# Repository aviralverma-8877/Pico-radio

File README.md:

# Raspberry Pi Pico Radio built on top of RDA5807

This project uses code from https://github.com/vmilea/pico_rda5807
Additionally it provide support for OLED display and handle GPIO input and output
for controlling an on board LED and Tact Switch.

For OLED display, This project uses pi_pico_ss_oled library from https://github.com/martinkooij/pi-pico-ss-oled

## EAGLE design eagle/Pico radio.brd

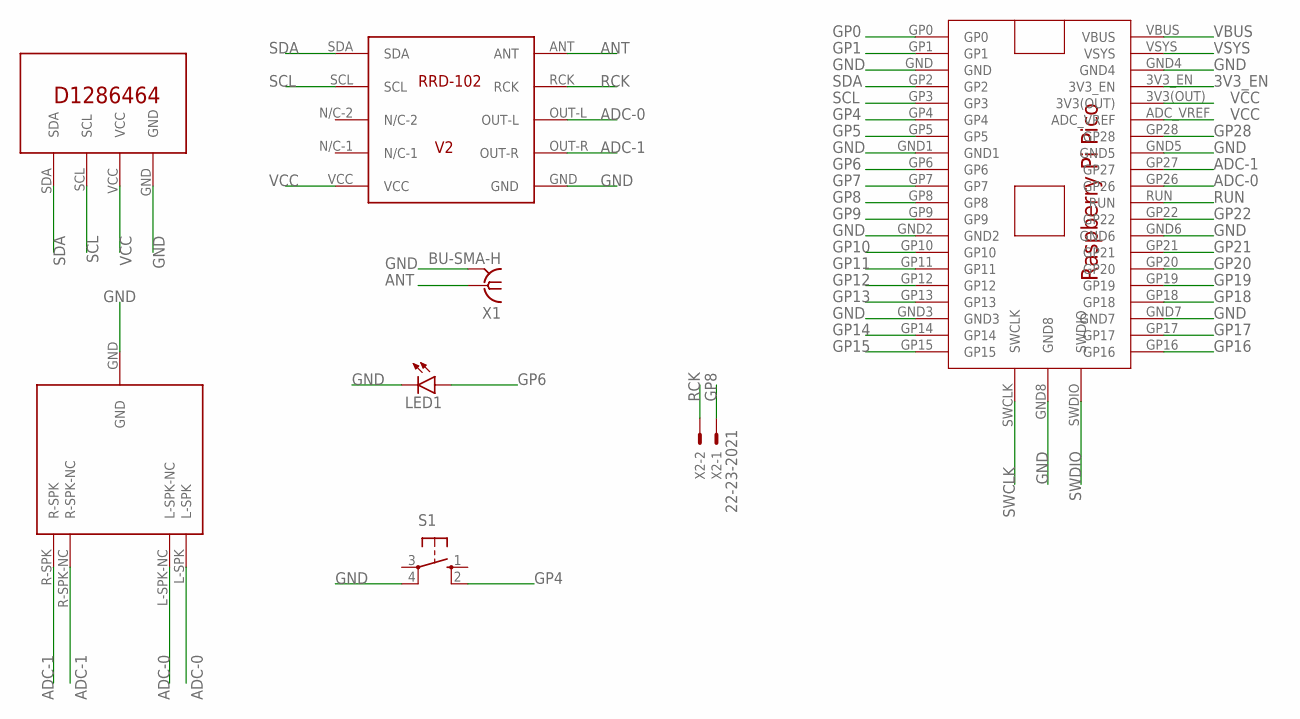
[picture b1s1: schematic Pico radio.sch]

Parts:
LED1: LED3MM
S1: 10-XX; B3F-10XX
U$1: OLED_DISPLAY
U$2: RASPBERRYPIPICO
U$3: RDD-V2
U$4: AUDIO_JACK
X1: BU-SMA-H
X2: 22-23-2021

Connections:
3V3_EN: U$2.3V3_EN
ADC-0: U$2.GP26, U$3.OUT-L, U$4.L-SPK, U$4.L-SPK-NC
ADC-1: U$2.GP27, U$3.OUT-R, U$4.R-SPK, U$4.R-SPK-NC
ANT: U$3.ANT, X1.1
GND: LED1.K (C), S1.4 (P1), U$1.GND, U$2.GND, U$2.GND1, U$2.GND2, U$2.GND3, U$2.GND4, U$2.GND5, U$2.GND6, U$2.GND7, U$2.GND8, U$3.GND, U$4.GND, X1.2, X1.3 (2), X1.4 (2), X1.5 (2)
GP0: U$2.GP0
GP1: U$2.GP1
GP4: S1.2 (S1), U$2.GP4
GP5: U$2.GP5
GP6: LED1.A, U$2.GP6
GP7: U$2.GP7
GP8: U$2.GP8, X2.1
GP9: U$2.GP9
GP10: U$2.GP10
GP11: U$2.GP11
GP12: U$2.GP12
GP13: U$2.GP13
GP14: U$2.GP14
GP15: U$2.GP15
GP16: U$2.GP16
GP17: U$2.GP17
GP18: U$2.GP18
GP19: U$2.GP19
GP20: U$2.GP20
GP21: U$2.GP21
GP22: U$2.GP22
GP28: U$2.GP28
RCK: U$3.RCK, X2.2
RUN: U$2.RUN
SCL: U$1.SCL, U$2.GP3, U$3.SCL
SDA: U$1.SDA, U$2.GP2, U$3.SDA
SWCLK: U$2.SWCLK
SWDIO: U$2.SWDIO
VBUS: U$2.VBUS
VCC: U$1.VCC, U$2.3V3(OUT), U$2.ADC_VREF, U$3.VCC
VSYS: U$2.VSYS

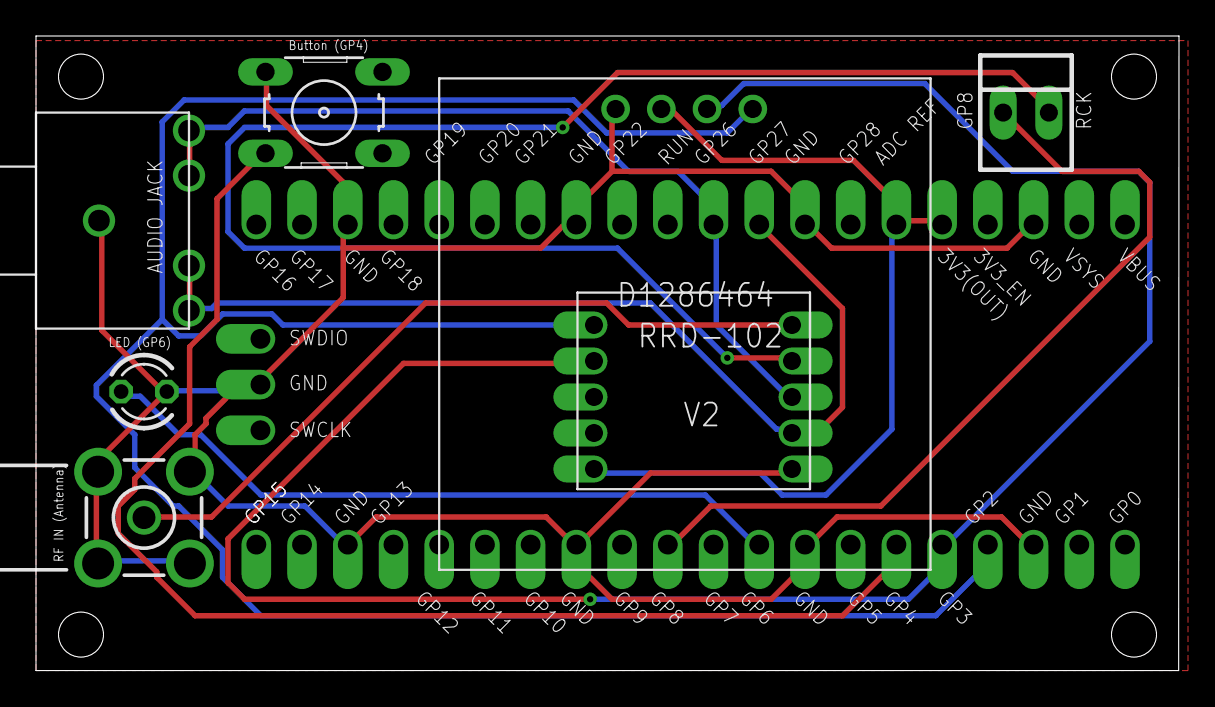
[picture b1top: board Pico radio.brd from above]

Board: 2 copper layers, 63.5 x 35.3 mm, 8 parts (1 on the bottom side), 11 nets.

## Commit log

2021-11-11 Code Changes
2021-11-11 Read Me modified
2021-11-11 3D Case Design Added
2021-12-21 Charging Indicator Added
2022-02-14 USB Control Added
2022-02-14 FM Station name changed
2022-02-16 Volume Amp added
2022-02-23 .gitignore added
2022-02-23 .vscode removed
